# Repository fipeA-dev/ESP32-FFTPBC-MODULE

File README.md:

# Firmware de Aquisição de Vibrações — ESP32 + 4x MPU9250

Firmware para aquisição simultânea de dados de 4 sensores MPU9250
em uma PCB baseada em ESP32 DevKit V1, preparado para posterior processamento
FFT.

## Como compilar

Projeto PlatformIO. Com a extensão do VS Code ou a CLI instalada:

```bash
pio run                 # compila
pio run -t upload       # grava no ESP32
pio device monitor       # abre o Serial Monitor (115200 baud)
```

## Estrutura do projeto

```
platformio.ini      -> configuração de build e dependências
include/pins.h       -> ÚNICA fonte de verdade sobre pinagem física
include/config.h     -> parâmetros de comportamento (endereços, tempos, escalas)
include/mpu.h        -> driver do MPU9250 (independente de barramento)
include/display.h    -> driver do LCD 16x2 via PCF8574 em I2C por software
include/buttons.h     -> classe Button com debounce não bloqueante
src/mpu.cpp
src/display.cpp
src/buttons.cpp
src/main.cpp          -> máquina de estados e laço principal
```

## Barramentos I2C

| Barramento          | Pinos          | Dispositivos          |
|---------------------|----------------|------------------------|
| Hardware `Wire`     | SDA 21 / SCL 22 | MPU1 (0x68), MPU2 (0x69) |
| Hardware `Wire1`    | SDA 32 / SCL 33 | MPU3 (0x68), MPU4 (0x69) |
| Software (bit-bang) | SDA 25 / SCL 26 | LCD 16x2 (PCF8574)     |

O LCD usa um barramento **totalmente isolado por software** (biblioteca
`SoftwareWire`)
## Máquina de estados

```
INITIALIZING -> (todos os dispositivos OK) -> READY
INITIALIZING -> (qualquer falha)           -> ERROR_STATE
READY        -> (botão START)              -> ACQUIRING
ACQUIRING    -> (tempo configurado esgotado) -> FINISHED
FINISHED     -> (botão START)              -> READY
ERROR_STATE  -> (botão START, nova tentativa) -> READY | ERROR_STATE
```

Nenhuma parte da lógica de estados usa `delay()`; toda a temporização é
feita comparando `millis()`. As únicas esperas ativas baseadas em
`micros()/millis()` existem exclusivamente na temporização de baixo nível
dos protocolos de hardware (reset do MPU, pulsos do HD44780), como em
qualquer driver de sensor/display — não bloqueiam a máquina de estados.

## Buffers de aquisição

Cada sensor possui seu próprio `std::vector<MpuSample>` em
`AcquisitionBuffers` (dentro de `main.cpp`), dimensionado (`reserve`) no
momento em que a aquisição começa, de acordo com o tempo configurado e a
taxa de amostragem (`Config::SAMPLE_RATE_HZ`, padrão 20 Hz).

> **Nota de engenharia:** o ESP32-WROOM-32 desta placa não possui PSRAM.
> A taxa de amostragem em `config.h` foi escolhida para caber com folga na
> SRAM disponível (~320 KB) mesmo na duração máxima de aquisição (120 s x 4
> sensores). Para taxas mais altas — recomendáveis para FFT de vibração de
> precisão — a extensão natural é fazer *streaming* direto para cartão SD
> em `saveBuffers()`/`readAllSensors()`, sem alterar o restante da
> arquitetura (ver seção abaixo).

## Extensões futuras (arquitetura já preparada)

- **FFT**: processar os `std::vector<MpuSample>` de `AcquisitionBuffers`
  logo após `saveBuffers()` — os dados já estão organizados por sensor e
  ordenados no tempo (`timestampMs`).
- **Cartão SD**: substituir/complementar o corpo de `saveBuffers()` por
  gravação em arquivo (ex.: um CSV por sensor); é o único ponto de
  integração necessário.
- **Wi-Fi / OTA / Interface Web**: podem ser inicializados em `setup()` e
  atualizados de forma cooperativa em `loop()`, pois nenhuma rotina do
  firmware bloqueia com `delay()`.
- **Bluetooth**: mesmo princípio — laço principal não bloqueante permite
  adicionar um serviço BLE sem reestruturar o código existente.

## Wiring resumido

| Sinal        | Pino ESP32 |
|--------------|------------|
| MPU1/2 SDA   | GPIO21     |
| MPU1/2 SCL   | GPIO22     |
| MPU3/4 SDA   | GPIO32     |
| MPU3/4 SCL   | GPIO33     |
| LCD SDA (SW) | GPIO25     |
| LCD SCL (SW) | GPIO26     |
| LED Status   | GPIO4 (via resistor 330 Ω para GND) |
| Botão START  | GPIO23 (para GND, INPUT_PULLUP) |
| Botão +      | GPIO14 (para GND, INPUT_PULLUP) |
| Botão -      | GPIO27 (para GND, INPUT_PULLUP) |

MPU1: AD0→GND (0x68) · MPU2: AD0→3V3 (0x69) · MPU3: AD0→GND (0x68) · MPU4: AD0→3V3 (0x69)

Os pinos dos MPUs foram removidos, devido a utilização deles em longas distâncias, a imagem mostra somente ponto de referencia daonde irá as outras plaquinhas bases de sensores descritas abaixo

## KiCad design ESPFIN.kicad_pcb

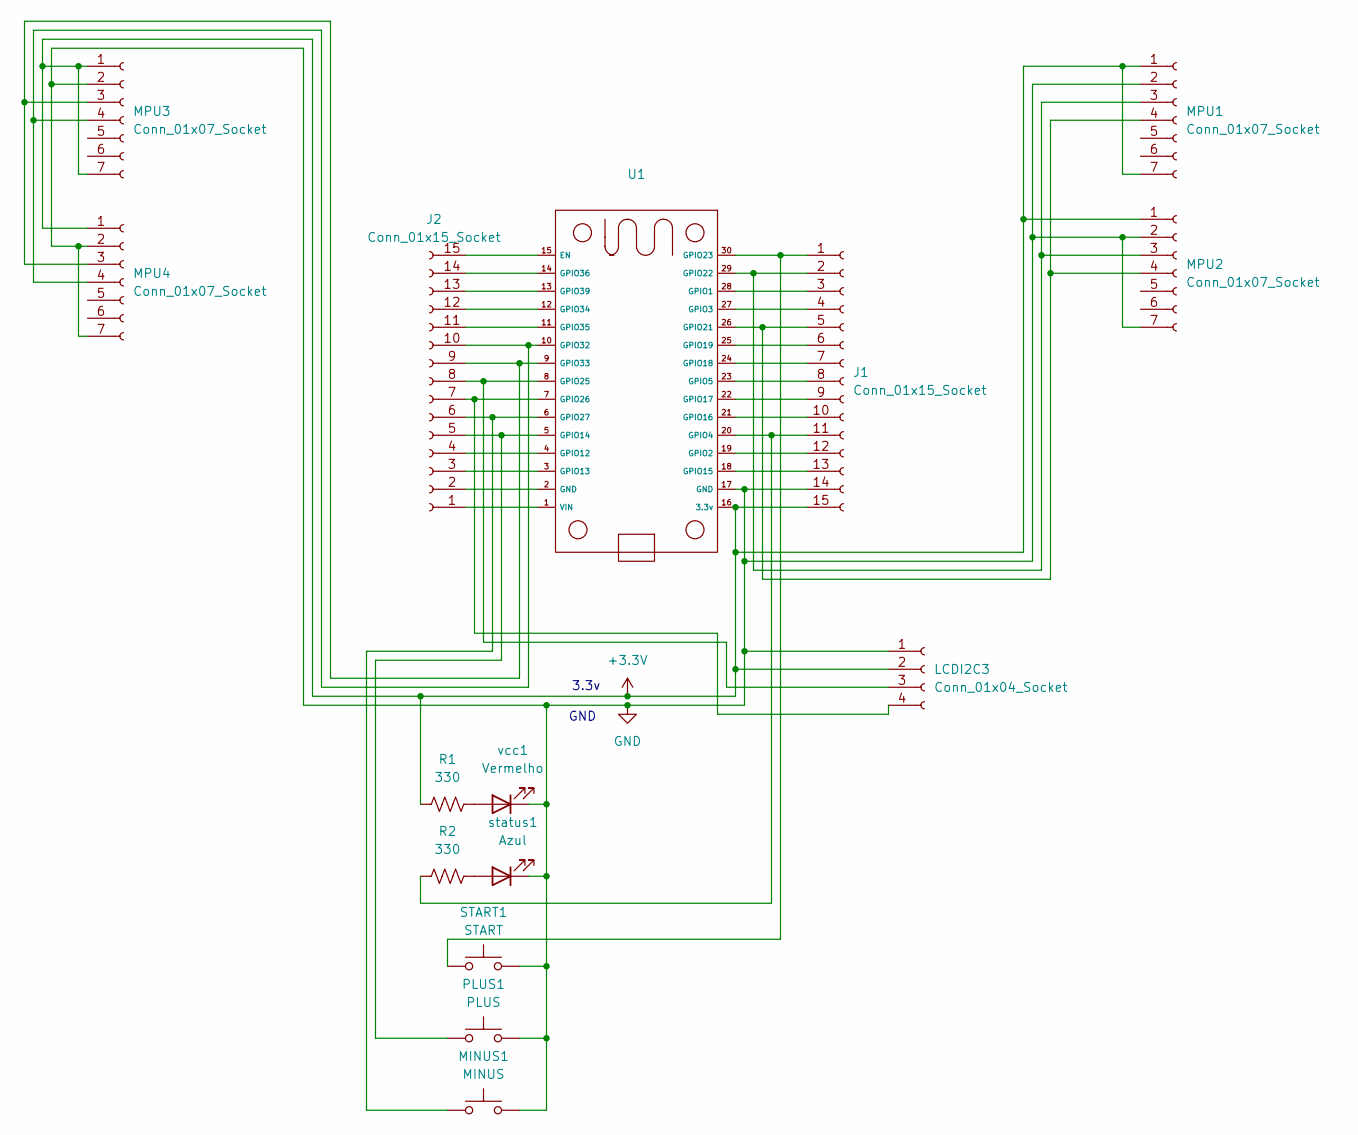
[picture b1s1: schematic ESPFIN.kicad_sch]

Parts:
J1, J2: Conn_01x15_Socket; PinSocket_1x15_P2.54mm_Vertical
LCDI2C3: Conn_01x04_Socket; PinSocket_1x04_P2.54mm_Horizontal
MINUS1: MINUS; SW_PUSH_6mm_H5mm
MPU1, MPU2, MPU3, MPU4: Conn_01x07_Socket; PinSocket_1x07_P2.54mm_Vertical
PLUS1: PLUS; SW_PUSH_6mm_H5mm
R1, R2: 330; R_Axial_DIN0207_L6.3mm_D2.5mm_P10.16mm_Horizontal
START1: START; SW_PUSH_6mm_H5mm
U1: (no value)
status1: Azul; LED_D3.0mm
vcc1: Vermelho; LED_D3.0mm

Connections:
+3.3V: J1.15, LCDI2C3.2, MPU1.1, MPU1.7, MPU2.1, MPU3.1, MPU3.7, MPU4.1, R1.2, U1.16 (3.3v)
GND: J1.14, LCDI2C3.1, MINUS1.2, MPU1.2, MPU2.2, MPU2.7, MPU3.2, MPU4.2, MPU4.7, PLUS1.2, START1.2, U1.17 (GND), status1.1 (K), vcc1.1 (K)
unnamed: J1.1, START1.1, U1.30 (GPIO23)
unnamed: J1.2, MPU1.3, MPU2.3, U1.29 (GPIO22)
unnamed: J1.3, U1.28 (GPIO1)
unnamed: J1.4, U1.27 (GPIO3)
unnamed: J1.5, MPU1.4, MPU2.4, U1.26 (GPIO21)
unnamed: J1.6, U1.25 (GPIO19)
unnamed: J1.7, U1.24 (GPIO18)
unnamed: J1.8, U1.23 (GPIO5)
unnamed: J1.9, U1.22 (GPIO17)
unnamed: J1.10, U1.21 (GPIO16)
unnamed: J1.11, R2.2, U1.20 (GPIO4)
unnamed: J1.12, U1.19 (GPIO2)
unnamed: J1.13, U1.18 (GPIO15)
unnamed: J2.1, U1.1 (VIN)
unnamed: J2.2, U1.2 (GND)
unnamed: J2.3, U1.3 (GPIO13)
unnamed: J2.4, U1.4 (GPIO12)
unnamed: J2.5, PLUS1.1, U1.5 (GPIO14)
unnamed: J2.6, MINUS1.1, U1.6 (GPIO27)
unnamed: J2.7, LCDI2C3.4, U1.7 (GPIO26)
unnamed: J2.8, LCDI2C3.3, U1.8 (GPIO25)
unnamed: J2.9, MPU3.3, MPU4.3, U1.9 (GPIO33)
unnamed: J2.10, MPU3.4, MPU4.4, U1.10 (GPIO32)
unnamed: J2.11, U1.11 (GPIO35)
unnamed: J2.12, U1.12 (GPIO34)
unnamed: J2.13, U1.13 (GPIO39)
unnamed: J2.14, U1.14 (GPIO36)
unnamed: J2.15, U1.15 (EN)
unnamed: R2.1, status1.2 (A)
unnamed: R1.1, vcc1.2 (A)

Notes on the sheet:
GND
3.3v

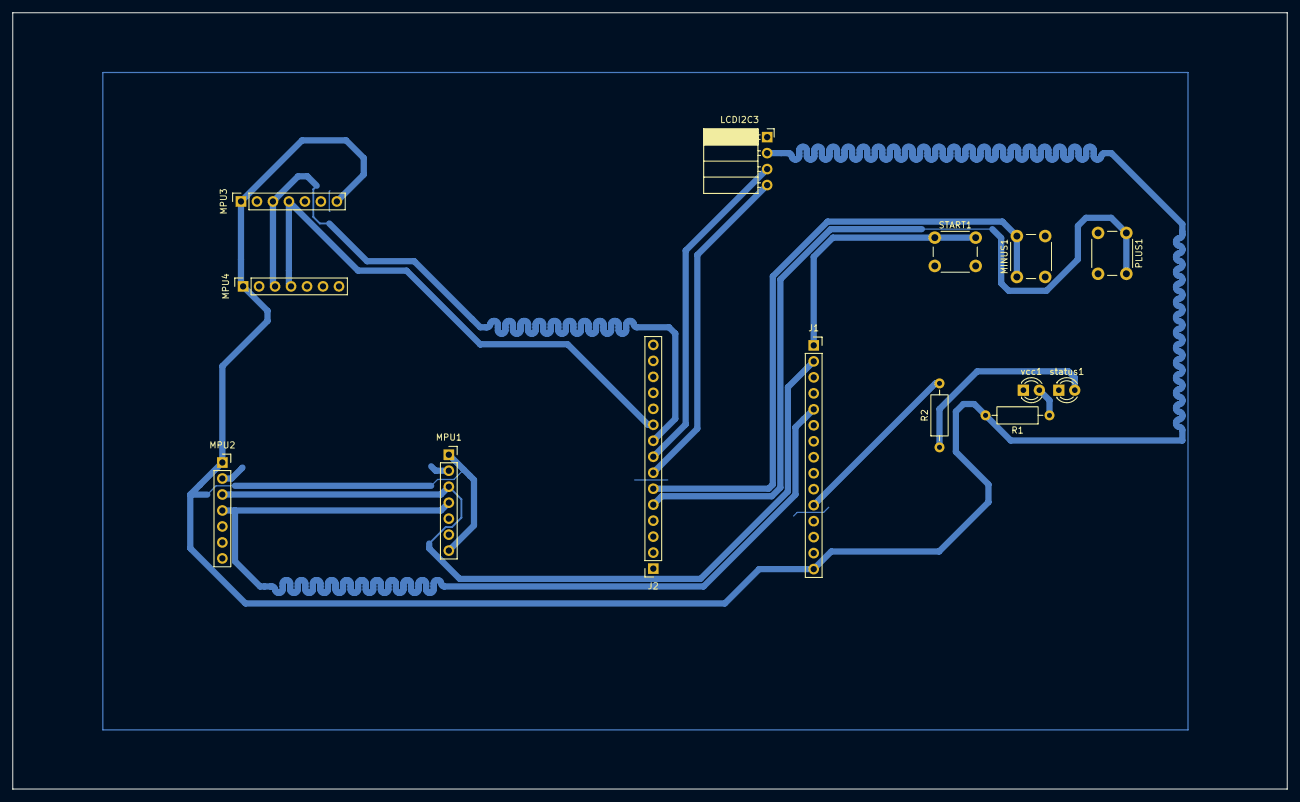
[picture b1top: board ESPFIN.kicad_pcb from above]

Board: 2 copper layers, 202.6 x 123.4 mm, 14 parts (0 on the bottom side), 14 nets.
